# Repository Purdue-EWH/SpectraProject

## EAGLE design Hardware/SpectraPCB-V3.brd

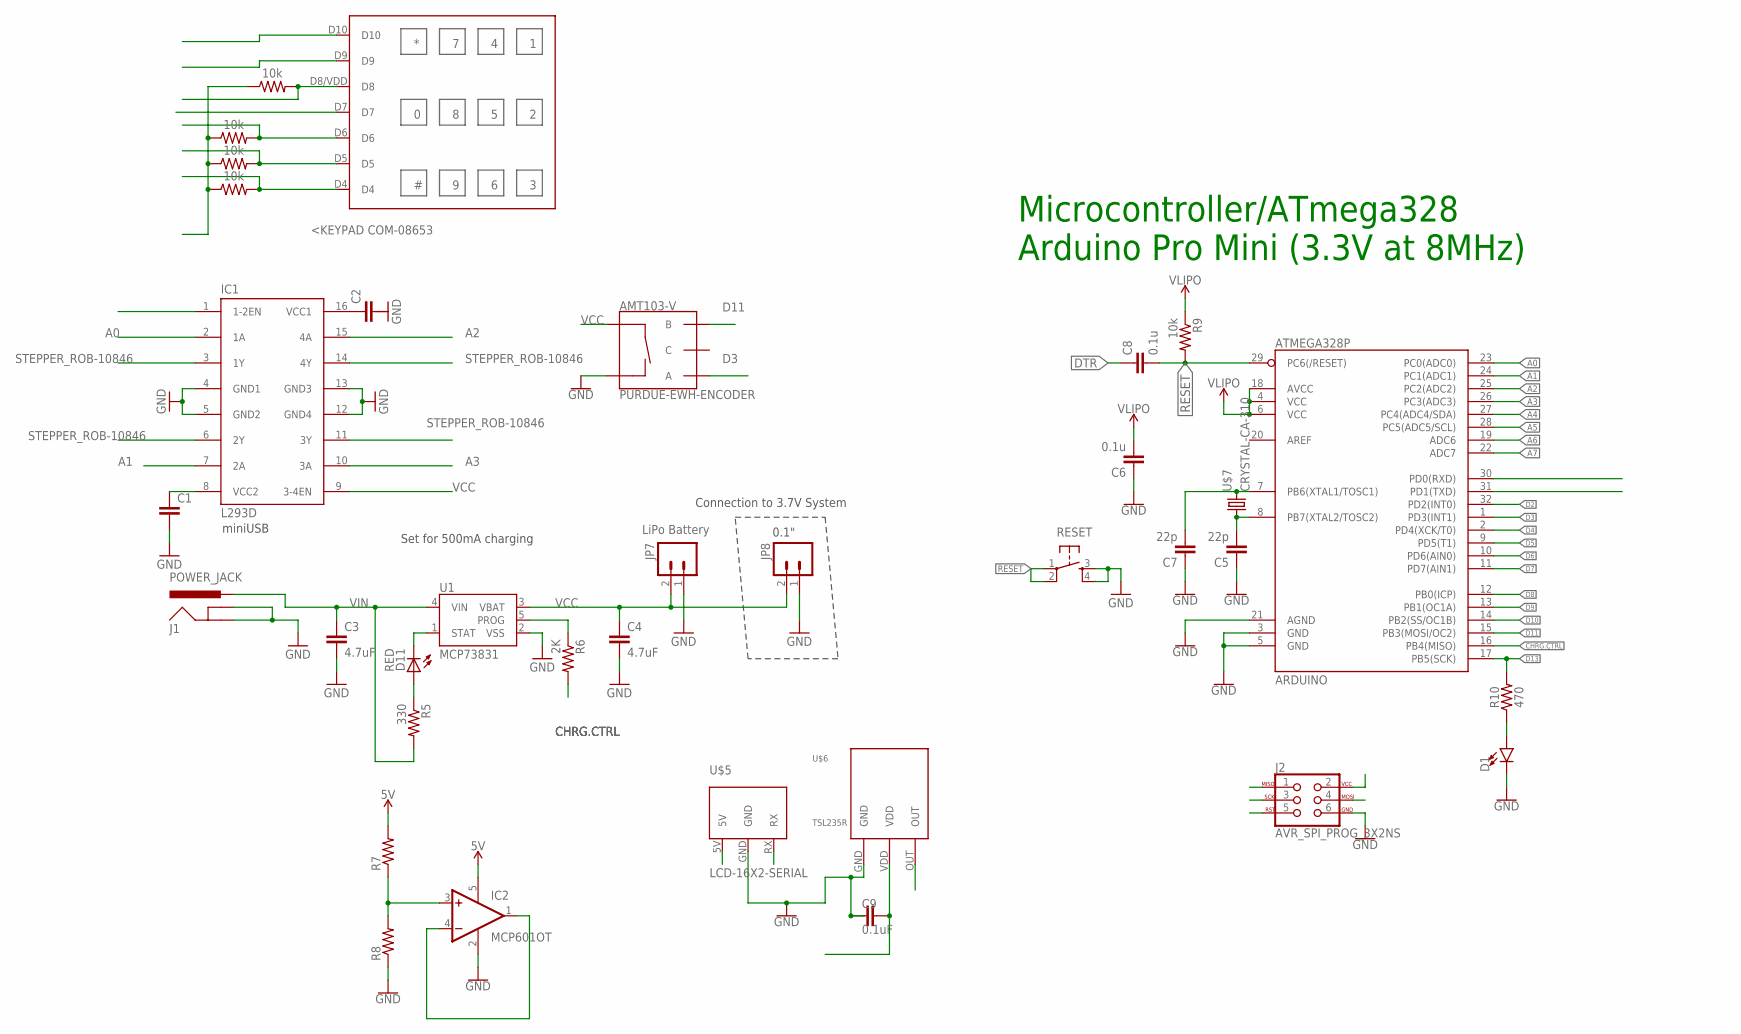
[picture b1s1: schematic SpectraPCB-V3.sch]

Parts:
AMT103-V: PURDUE-EWH-ENCODER
ARDUINO: ATMEGA328P; TQFP32-08
C1: C-EUC0603; C0603
C2: C-EUC0402; C0402
C3, C4: 4.7uF; 0402-CAP
C5, C7: 22p; C0402
C6, C8: 0.1u; C0402
C9: 0.1uF; 0603
D1: LED5MM; LED_5MM
D11: RED; LED-0603
IC1: L293D; DIL16
IC2: MCP601OT; SOT23-5
J1: POWER_JACK; POWER_JACK_PTH
J2: AVR_SPI_PROG_3X2NS; 2X3-NS
JP7: LiPo Battery; JST-2-SMD
JP8: M02PTH; 1X02
R1, R2, R3, R4: 10k; 0603
R5: 330; 0402-RES
R6: 2K; 0402-RES
R7, R8: R-US_R0402; R0402
R9: 10k; R0402
R10: 470; 0603
RESET: BUTTON-PTS830GG140; BUTTON-GULLWING
U1: MCP73831; SOT23-5
U$1: EWH_KEYPAD
U$5: LCD-16X2-SERIAL
U$6: TSL235R
U$7: CRYSTAL-CA-310; CA-301

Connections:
5V: IC2.5 (V+), R7.2
A0: ARDUINO.23 (PC0(ADC0)), IC1.2 (1A)
A1: ARDUINO.24 (PC1(ADC1)), IC1.7 (2A)
A2: ARDUINO.25 (PC2(ADC2)), IC1.15 (4A)
A3: ARDUINO.26 (PC3(ADC3)), IC1.10 (3A)
A4: ARDUINO.27 (PC4(ADC4/SDA))
A5: ARDUINO.28 (PC5(ADC5/SCL))
A6: ARDUINO.19 (ADC6)
A7: ARDUINO.22 (ADC7)
CHRG.CTRL: ARDUINO.16 (PB4(MISO)), R6.2
D0: ARDUINO.30 (PD0(RXD))
D1: ARDUINO.31 (PD1(TXD)), U$5.RX
D2: ARDUINO.32 (PD2(INT0)), U$6.OUT
D3: AMT103-V.A, ARDUINO.1 (PD3(INT1))
D4: ARDUINO.2 (PD4(XCK/T0)), R4.2, U$1.D4
D5: ARDUINO.9 (PD5(T1)), R3.2, U$1.D5
D6: ARDUINO.10 (PD6(AIN0)), R2.2, U$1.D6
D7: ARDUINO.11 (PD7(AIN1)), U$1.D7
D8: ARDUINO.12 (PB0(ICP)), R1.2, U$1.D8/VDD (D8)
D9: ARDUINO.13 (PB1(OC1A)), U$1.D9
D10: ARDUINO.14 (PB2(SS/OC1B)), U$1.D10
D11: AMT103-V.B, ARDUINO.15 (PB3(MOSI/OC2))
D13: ARDUINO.17 (PB5(SCK)), R10.2
DTR: C8.1
GND: AMT103-V.SW-, ARDUINO.3 (GND), ARDUINO.5 (GND), ARDUINO.21 (AGND), C1.2, C3.2, C4.2, C5.1, C6.1, C7.1, C9.1, D1.K (C), IC1.4 (GND1), IC1.5 (GND2), IC1.12 (GND4), IC1.13 (GND3), IC2.2 (V-), J1.GND, J1.GNDBREAK, J2.6, JP7.1, JP8.1, R8.1, RESET.3, RESET.4, U1.2 (VSS), U$5.GND, U$6.GND
unnamed: C1.1, IC1.8 (VCC2)
unnamed: C2.1, IC1.16 (VCC1)
unnamed: D11.A, R5.1
unnamed: IC2.3 (+IN), R7.1, R8.2
unnamed: IC2.1 (OUT), IC2.4 (-IN)
unnamed: ARDUINO.7 (PB6(XTAL1/TOSC1)), C7.2, U$7.2
unnamed: ARDUINO.8 (PB7(XTAL2/TOSC2)), C5.2, U$7.1
unnamed: D1.A, R10.1
PROG: R6.1, U1.5 (PROG)
RESET: ARDUINO.29 (PC6(/RESET)), C8.2, R9.2, RESET.1, RESET.2
STAT: D11.C, U1.1 (STAT)
STEPPER_ROB-10846: IC1.3 (1Y), IC1.6 (2Y), IC1.11 (3Y), IC1.14 (4Y)
VCC: AMT103-V.SW+, C4.1, C9.2, IC1.1 (1-2EN), IC1.9 (3-4EN), JP7.2, JP8.2, U1.3 (VBAT), U$5.5V, U$6.VDD
VDD: R1.1, R2.1, R3.1, R4.1
VIN: C3.1, J1.PWR, R5.2, U1.4 (VIN)
VLIPO: ARDUINO.4 (VCC), ARDUINO.6 (VCC), ARDUINO.18 (AVCC), C6.2, R9.1

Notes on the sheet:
<KEYPAD COM-08653
Set for 500mA charging
Connection to 3.7V System
0.1"
miniUSB
Microcontroller/ATmega328 Arduino Pro Mini (3.3V at 8MHz)

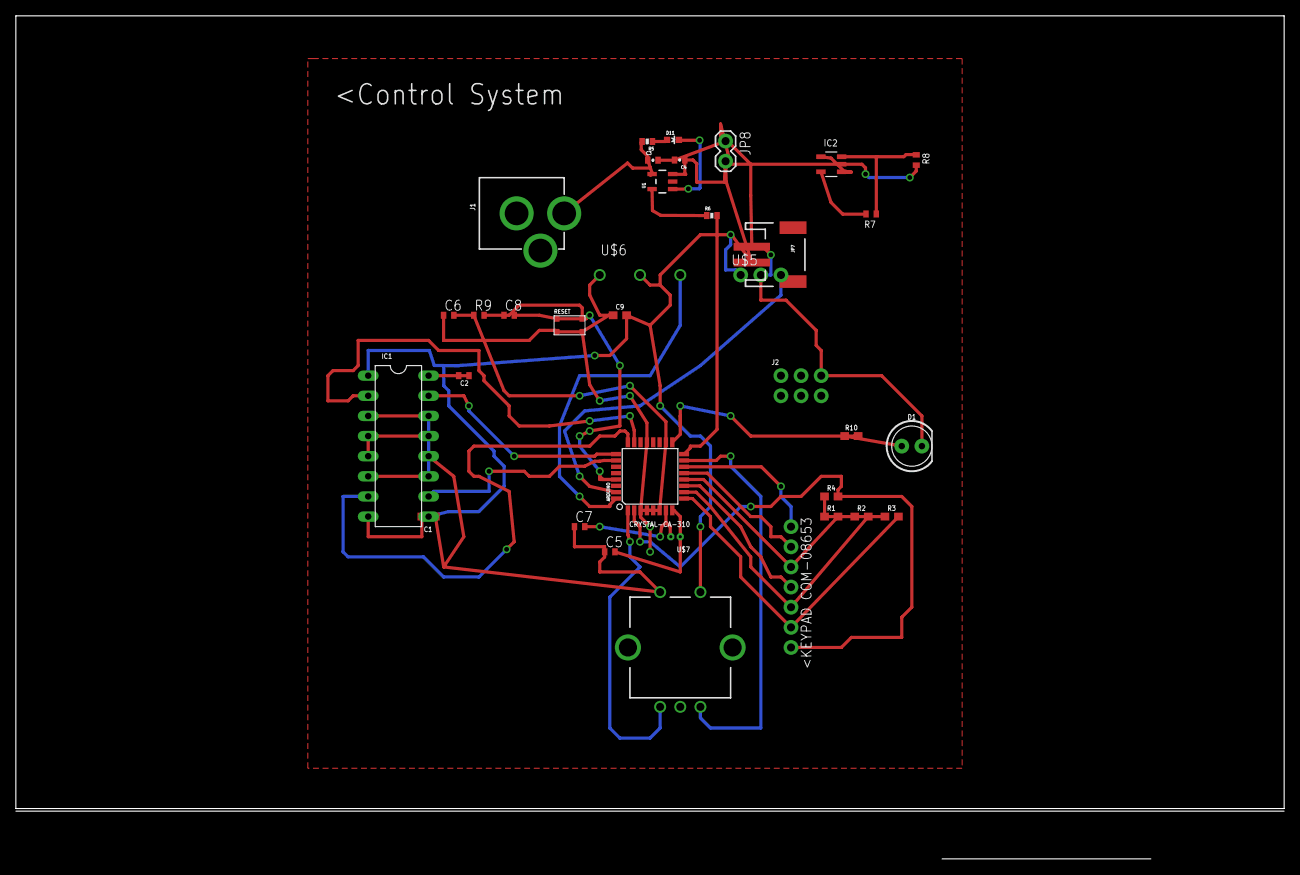
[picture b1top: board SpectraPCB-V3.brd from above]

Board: 2 copper layers, 160.0 x 106.3 mm, 35 parts (0 on the bottom side), 35 nets.

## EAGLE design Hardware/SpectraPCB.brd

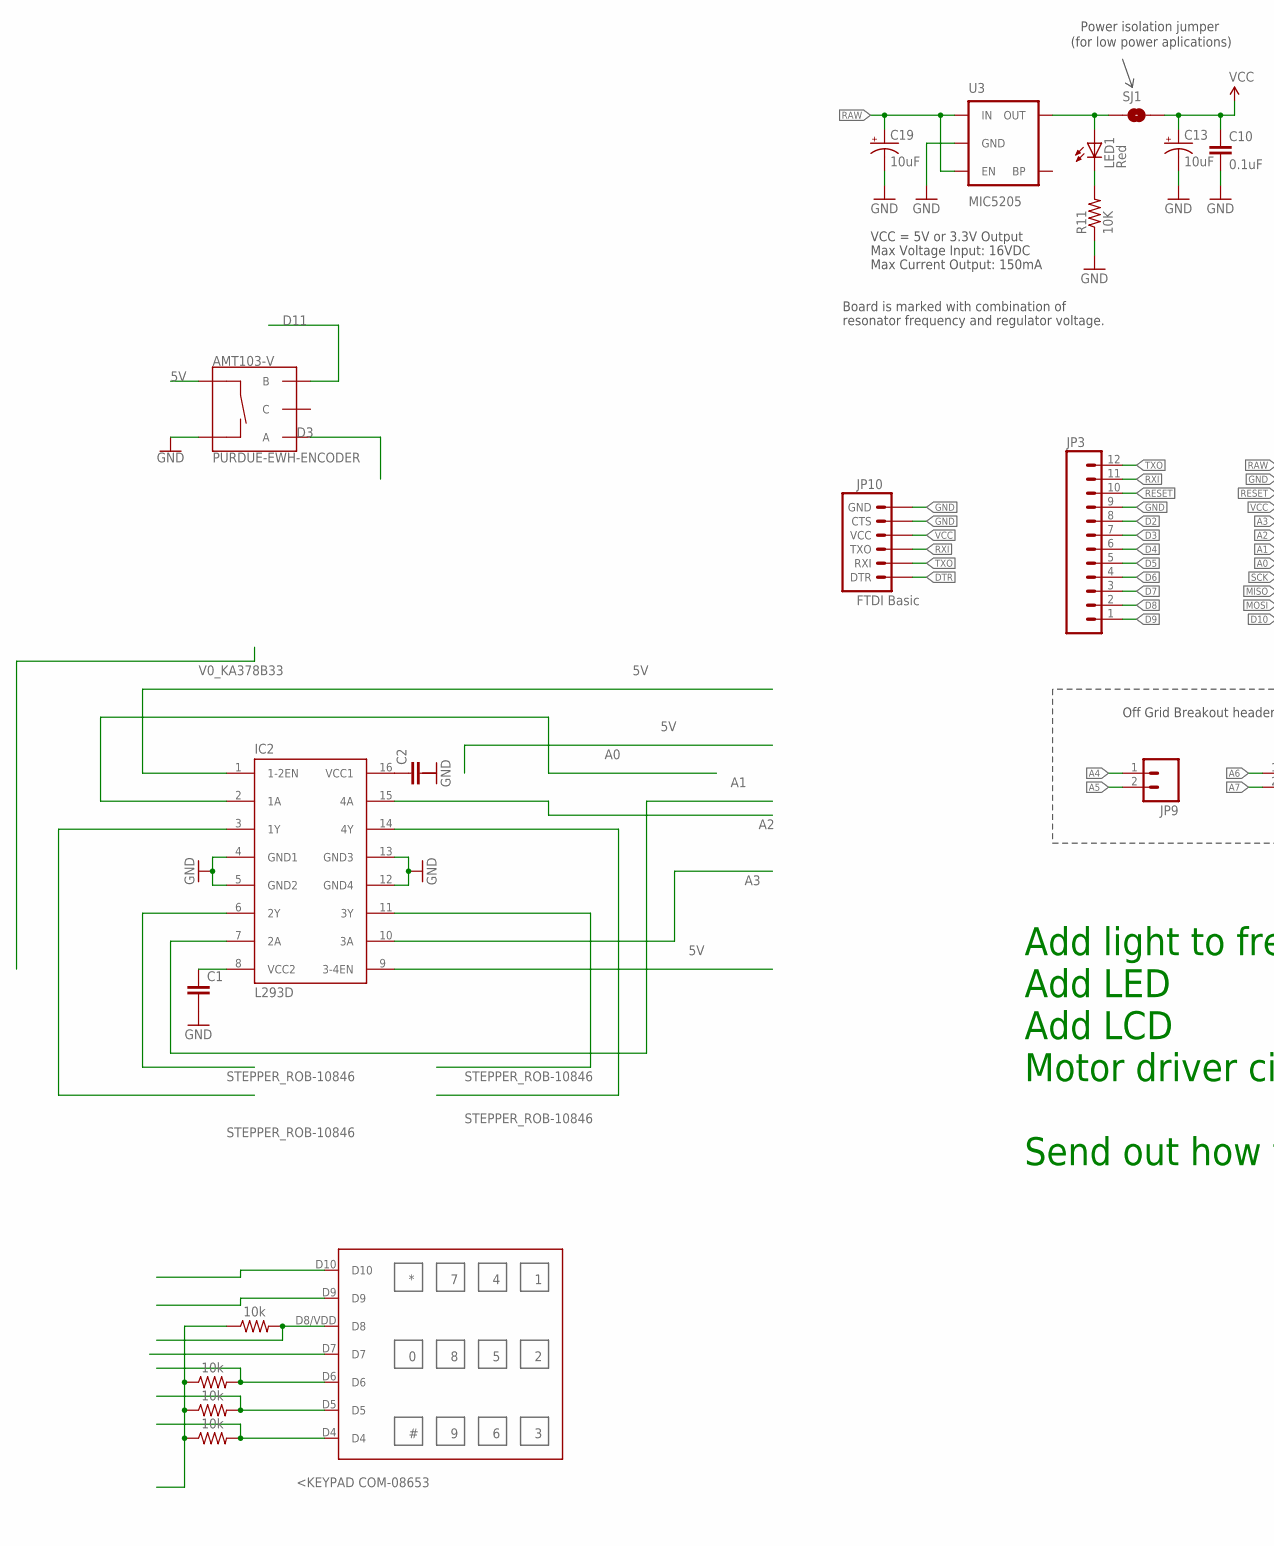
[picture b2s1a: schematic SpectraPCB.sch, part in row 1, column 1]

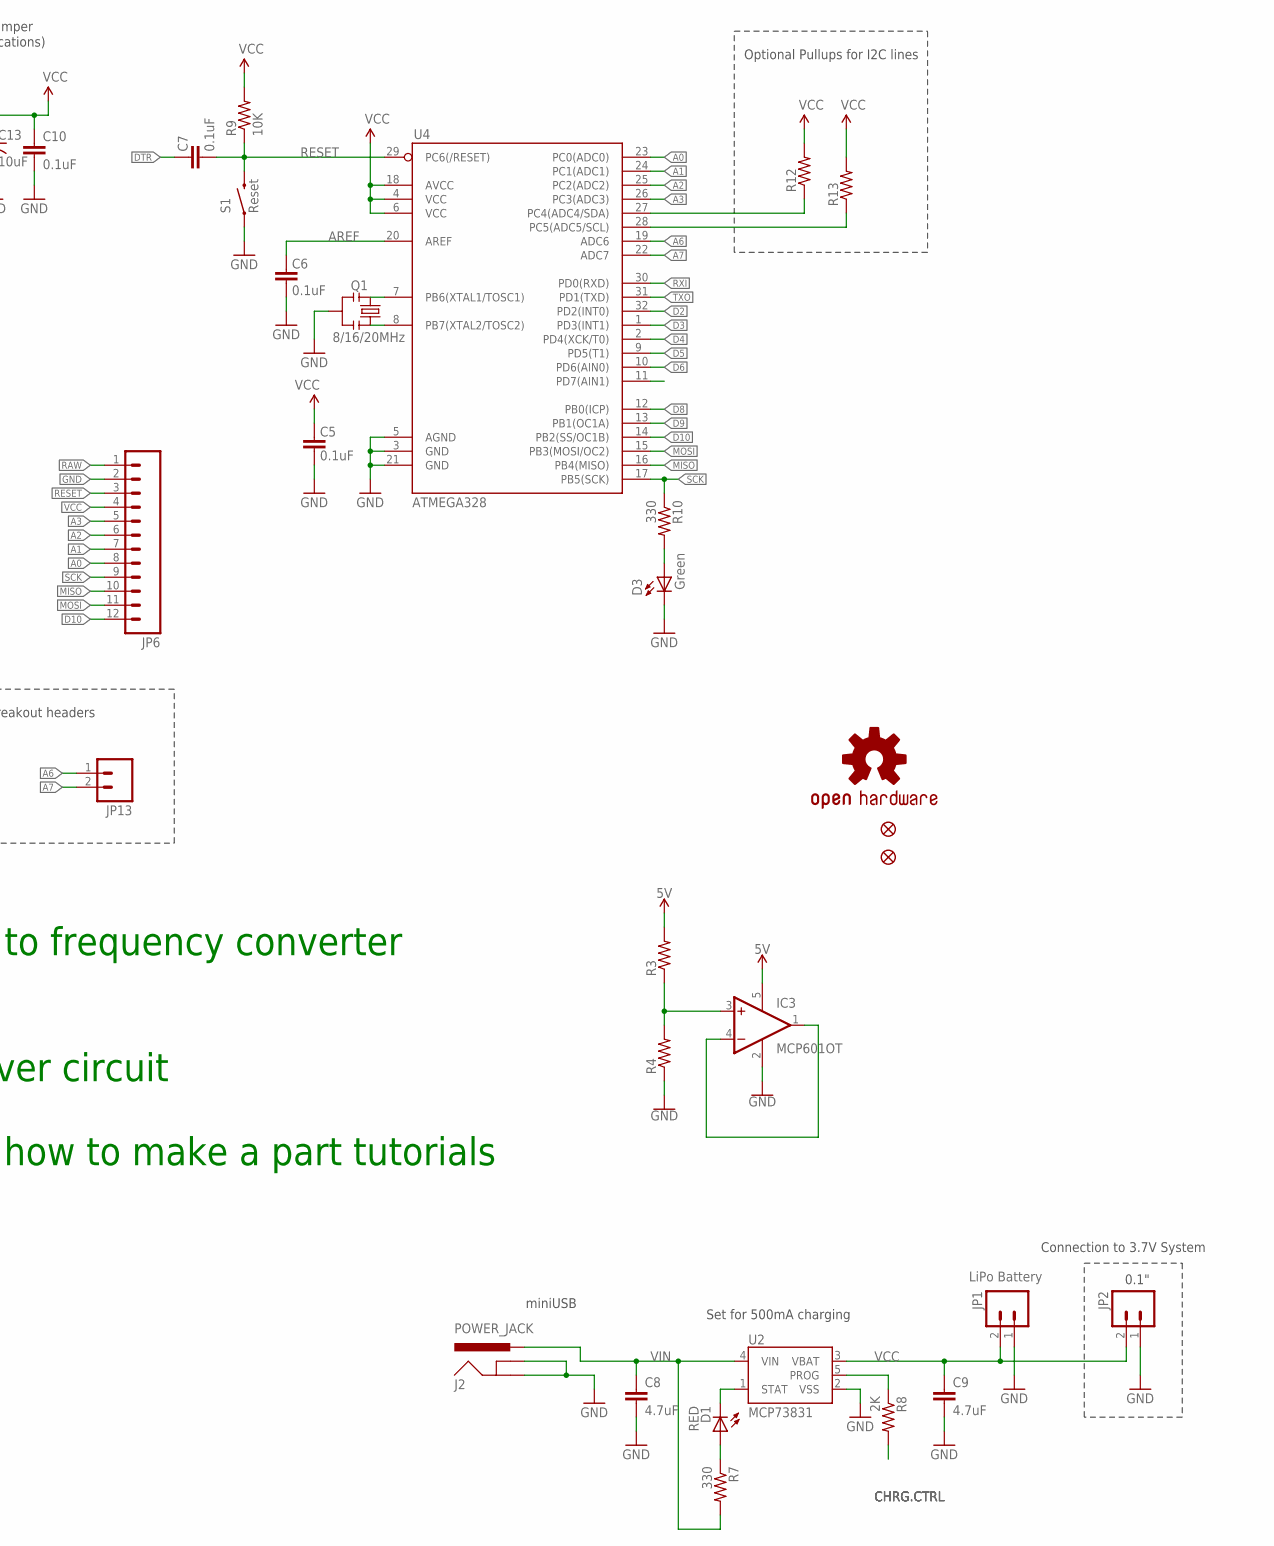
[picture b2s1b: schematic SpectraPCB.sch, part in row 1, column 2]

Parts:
AMT103-V: PURDUE-EWH-ENCODER
C1: C-EUC0603; C0603
C2: C-EUC0402; C0402
C5, C6, C7, C10: 0.1uF; 0603-CAP
C8, C9: 4.7uF; 0402-CAP
C13, C19: 10uF; EIA3216
D1: RED; LED-0603
D3: Green; 0603-LED-ALT1
IC2: L293D; DIL16
IC3: MCP601OT; SOT23-5
J2: POWER_JACK; POWER_JACK_PTH
JP1: LiPo Battery; JST-2-SMD
JP2, JP9, JP13: M02PTH; 1X02
JP3, JP6: M12PTH; 1X12
JP10: FTDI Basic; 1X06
JP11, JP12: FIDUCIALUFIDUCIAL; MICRO-FIDUCIAL
LED1: Red; 0603-LED-ALT1
Q1: 8/16/20MHz; RESONATOR-SMD-1:1
R1, R2, R5, R6: 10k; 0603
R3, R4: R-US_R0402; R0402
R7: 330; 0402-RES
R8: 2K; 0402-RES
R9, R11: 10K; 0603-RES
R10: 330; 0603-RES
R12, R13: RESISTOR0603-RES; 0603-RES
S1: Reset; TACTILE-SWITCH-SMD-ALT01
SJ1: SOLDERJUMPERNC; SJ_2S
U2: MCP73831; SOT23-5
U3: MIC5205; SOT23-5
U4: ATMEGA328; TQFP32-08
U$1: EWH_KEYPAD
U$3: OSHW-LOGOS; OSHW-LOGO-S

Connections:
5V: AMT103-V.SW+, IC2.1 (1-2EN), IC2.9 (3-4EN), IC3.5 (V+), R3.2
A0: IC2.2 (1A), JP6.8, U4.23 (PC0(ADC0))
A1: IC2.7 (2A), JP6.7, U4.24 (PC1(ADC1))
A2: IC2.15 (4A), JP6.6, U4.25 (PC2(ADC2))
A3: IC2.10 (3A), JP6.5, U4.26 (PC3(ADC3))
A4: JP9.1, R12.1, U4.27 (PC4(ADC4/SDA))
A5: JP9.2, R13.1, U4.28 (PC5(ADC5/SCL))
A6: JP13.1, U4.19 (ADC6)
A7: JP13.2, U4.22 (ADC7)
AREF: C6.2, U4.20 (AREF)
CHRG.CTRL: R8.2, U4.11 (PD7(AIN1))
D2: JP3.8, U4.32 (PD2(INT0))
D3: AMT103-V.A, JP3.7, U4.1 (PD3(INT1))
D4: JP3.6, U4.2 (PD4(XCK/T0))
D5: JP3.5, U4.9 (PD5(T1))
D6: JP3.4, U4.10 (PD6(AIN0))
D7: JP3.3
D8: JP3.2, U4.12 (PB0(ICP))
D9: JP3.1, U4.13 (PB1(OC1A))
D10: JP6.12, U4.14 (PB2(SS/OC1B))
D11: AMT103-V.B
DTR: C7.2, JP10.1 (DTR)
GND: AMT103-V.SW-, C1.2, C5.1, C6.1, C8.2, C9.2, C10.2, C13.C (-), C19.C (-), D3.C, IC2.4 (GND1), IC2.5 (GND2), IC2.12 (GND4), IC2.13 (GND3), IC3.2 (V-), J2.GND, J2.GNDBREAK, JP1.1, JP2.1, JP3.9, JP6.2, JP10.5 (CTS), JP10.6 (GND), Q1.2, R4.1, R11.1, S1.1, S1.2 (1), U2.2 (VSS), U3.2 (GND), U4.3 (GND), U4.5 (AGND), U4.21 (GND)
MISO: JP6.10, U4.16 (PB4(MISO))
MOSI: JP6.11, U4.15 (PB3(MOSI/OC2))
unnamed: Q1.3, U4.8 (PB7(XTAL2/TOSC2))
unnamed: C1.1, IC2.8 (VCC2)
unnamed: IC3.3 (+IN), R3.1, R4.2
unnamed: Q1.1, U4.7 (PB6(XTAL1/TOSC1))
unnamed: LED1.A, SJ1.1, U3.5 (OUT)
unnamed: LED1.C, R11.2
unnamed: D3.A, R10.2
unnamed: C2.1, IC2.16 (VCC1)
unnamed: R1.2, U$1.D8/VDD (D8)
unnamed: R2.2, U$1.D6
unnamed: R6.2, U$1.D4
unnamed: R1.1, R2.1, R5.1, R6.1
unnamed: R5.2, U$1.D5
unnamed: D1.A, R7.1
unnamed: IC3.1 (OUT), IC3.4 (-IN)
PROG1: R8.1, U2.5 (PROG)
RAW: C19.A (+), JP6.1, U3.1 (IN), U3.3 (EN)
RESET: C7.1, JP3.10, JP6.3, R9.1, S1.3 (2), S1.4 (2), U4.29 (PC6(/RESET))
RXI: JP3.11, JP10.3 (TXO), U4.30 (PD0(RXD))
SCK: JP6.9, R10.1, U4.17 (PB5(SCK))
STAT1: D1.C, U2.1 (STAT)
STEPPER_ROB-10846: IC2.3 (1Y), IC2.6 (2Y), IC2.11 (3Y), IC2.14 (4Y)
TXO: JP3.12, JP10.2 (RXI), U4.31 (PD1(TXD))
VCC: C5.2, C9.1, C10.1, C13.A (+), JP1.2, JP2.2, JP6.4, JP10.4 (VCC), R9.2, R12.2, R13.2, SJ1.2, U2.3 (VBAT), U4.4 (VCC), U4.6 (VCC), U4.18 (AVCC)
VIN: C8.1, J2.PWR, R7.2, U2.4 (VIN)

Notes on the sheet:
Max Voltage Input: 16VDC
Max Current Output: 150mA
Board is marked with combination of
resonator frequency and regulator voltage.
VCC = 5V or 3.3V Output
Optional Pullups for I2C lines
Off Grid Breakout headers
Power isolation jumper
(for low power aplications)
Add light to frequency converter Add LED Add LCD Motor driver circuit Send out how to make a part tutorials
<KEYPAD COM-08653
Set for 500mA charging
Connection to 3.7V System
0.1"
miniUSB

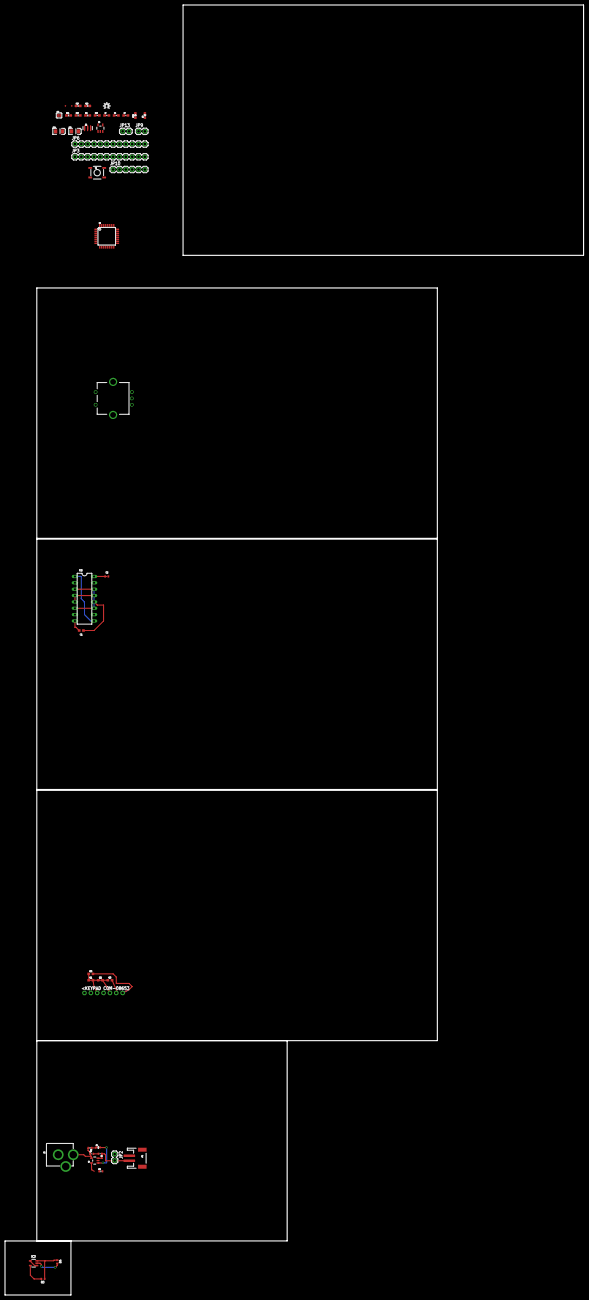
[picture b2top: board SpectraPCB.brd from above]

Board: 2 copper layers, 231.1 x 515.3 mm, 47 parts (0 on the bottom side), 48 nets.

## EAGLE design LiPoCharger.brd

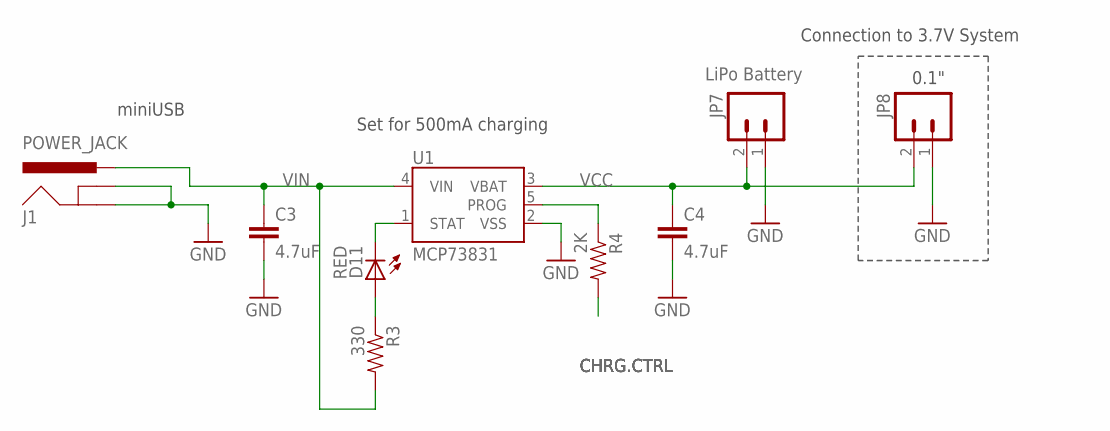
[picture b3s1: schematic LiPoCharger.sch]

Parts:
C3, C4: 4.7uF; 0402-CAP
D11: RED; LED-0603
J1: POWER_JACK; POWER_JACK_PTH
JP7: LiPo Battery; JST-2-SMD
JP8: M02PTH; 1X02
R3: 330; 0402-RES
R4: 2K; 0402-RES
U1: MCP73831; SOT23-5

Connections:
CHRG.CTRL: R4.2
GND: C3.2, C4.2, J1.GND, J1.GNDBREAK, JP7.1, JP8.1, U1.2 (VSS)
unnamed: D11.A, R3.1
PROG: R4.1, U1.5 (PROG)
STAT: D11.C, U1.1 (STAT)
VCC: C4.1, JP7.2, JP8.2, U1.3 (VBAT)
VIN: C3.1, J1.PWR, R3.2, U1.4 (VIN)

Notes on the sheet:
Set for 500mA charging
Connection to 3.7V System
0.1"
miniUSB

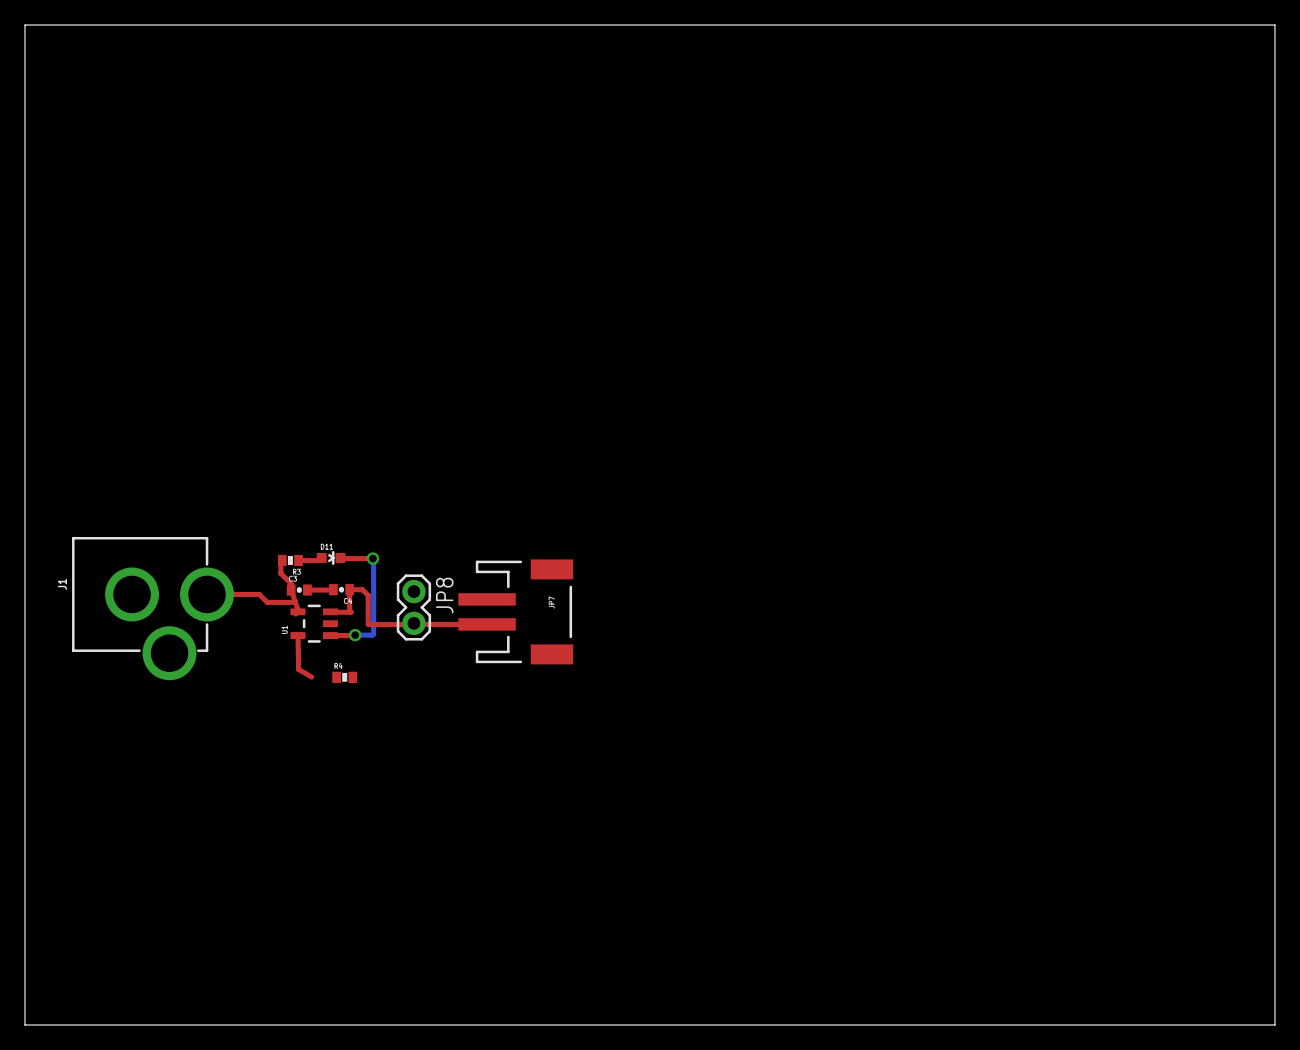
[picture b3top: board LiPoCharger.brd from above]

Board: 2 copper layers, 100.0 x 80.0 mm, 9 parts (0 on the bottom side), 6 nets.

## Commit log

2017-02-13 initial code
2017-02-14 added preliminary circuit schematic
2017-02-21 added Mitchell_Hoge.docx
2017-02-21 added MITCHELLHOGE.docx
2017-02-23 Jacqueline Chau
2017-02-25 Added AsifAshraful.docx
2017-03-06 Ya boy
2017-04-03 adding all the design blocks
2017-04-10 Added Updated PCB Specta
2017-04-10 remade sch and brd files
2017-04-15 Updated SpectaPCB-V3

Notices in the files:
parts and their libraries:
SparkFun-Resistors: Licensing: Creative Commons ShareAlike 4.0 International - https://creativecommons.org/licenses/by-sa/4.0
SparkFun-Passives: Licensing: CC v3.0 Share-Alike You are welcome to use this library for commercial purposes.
